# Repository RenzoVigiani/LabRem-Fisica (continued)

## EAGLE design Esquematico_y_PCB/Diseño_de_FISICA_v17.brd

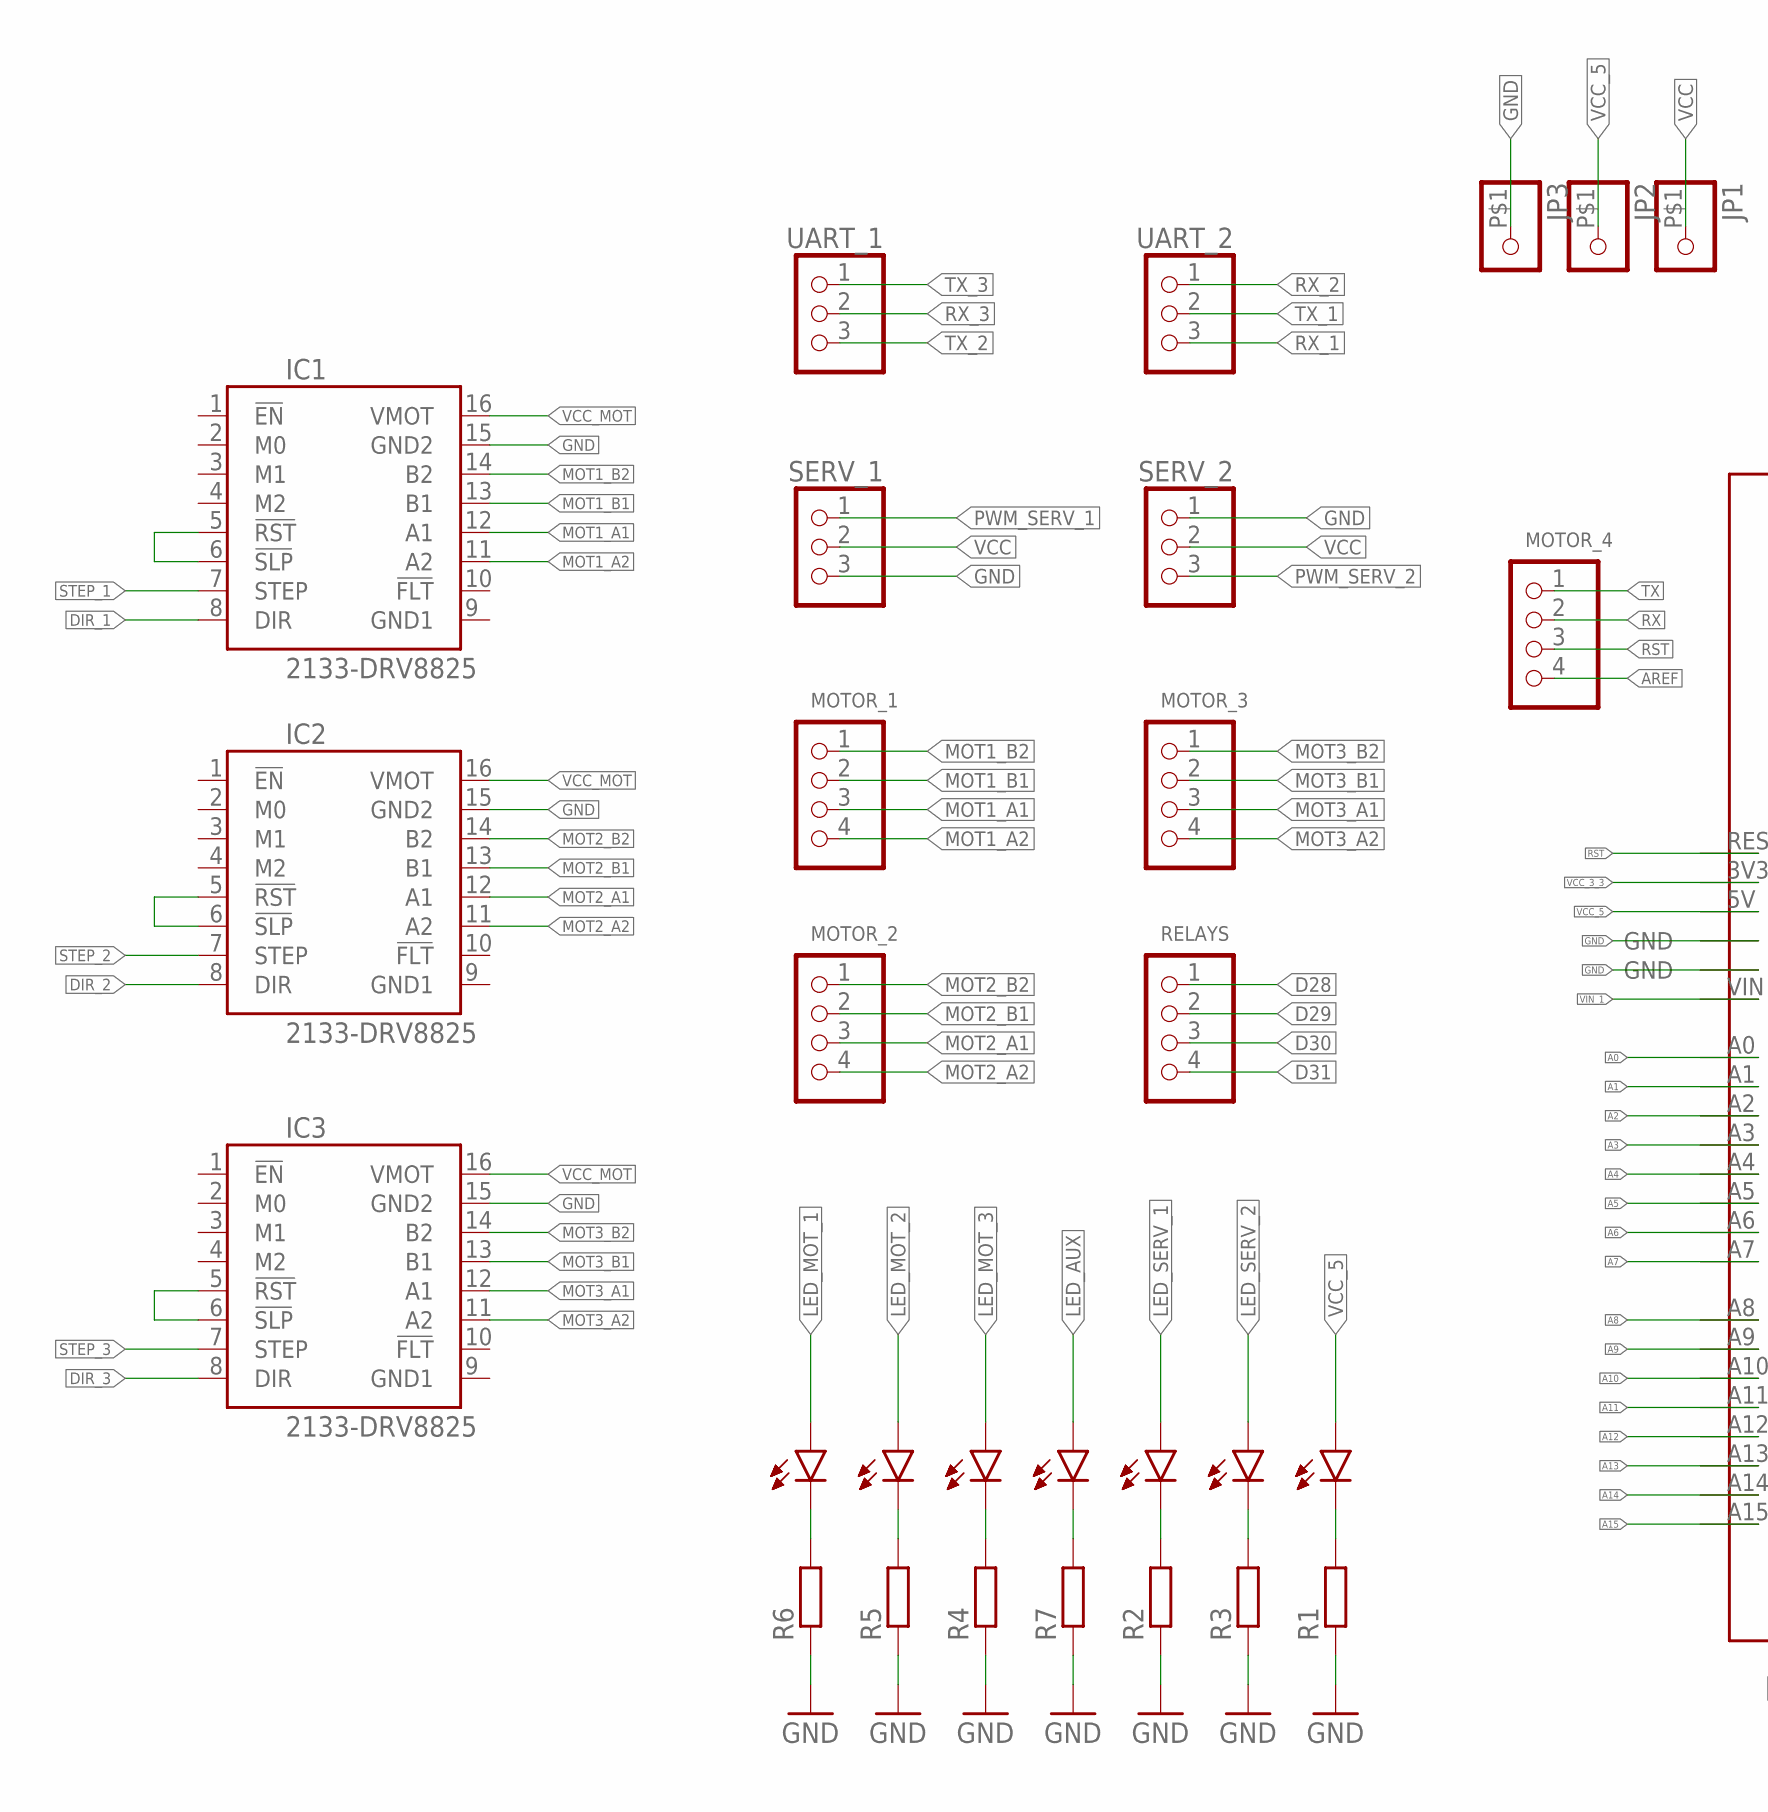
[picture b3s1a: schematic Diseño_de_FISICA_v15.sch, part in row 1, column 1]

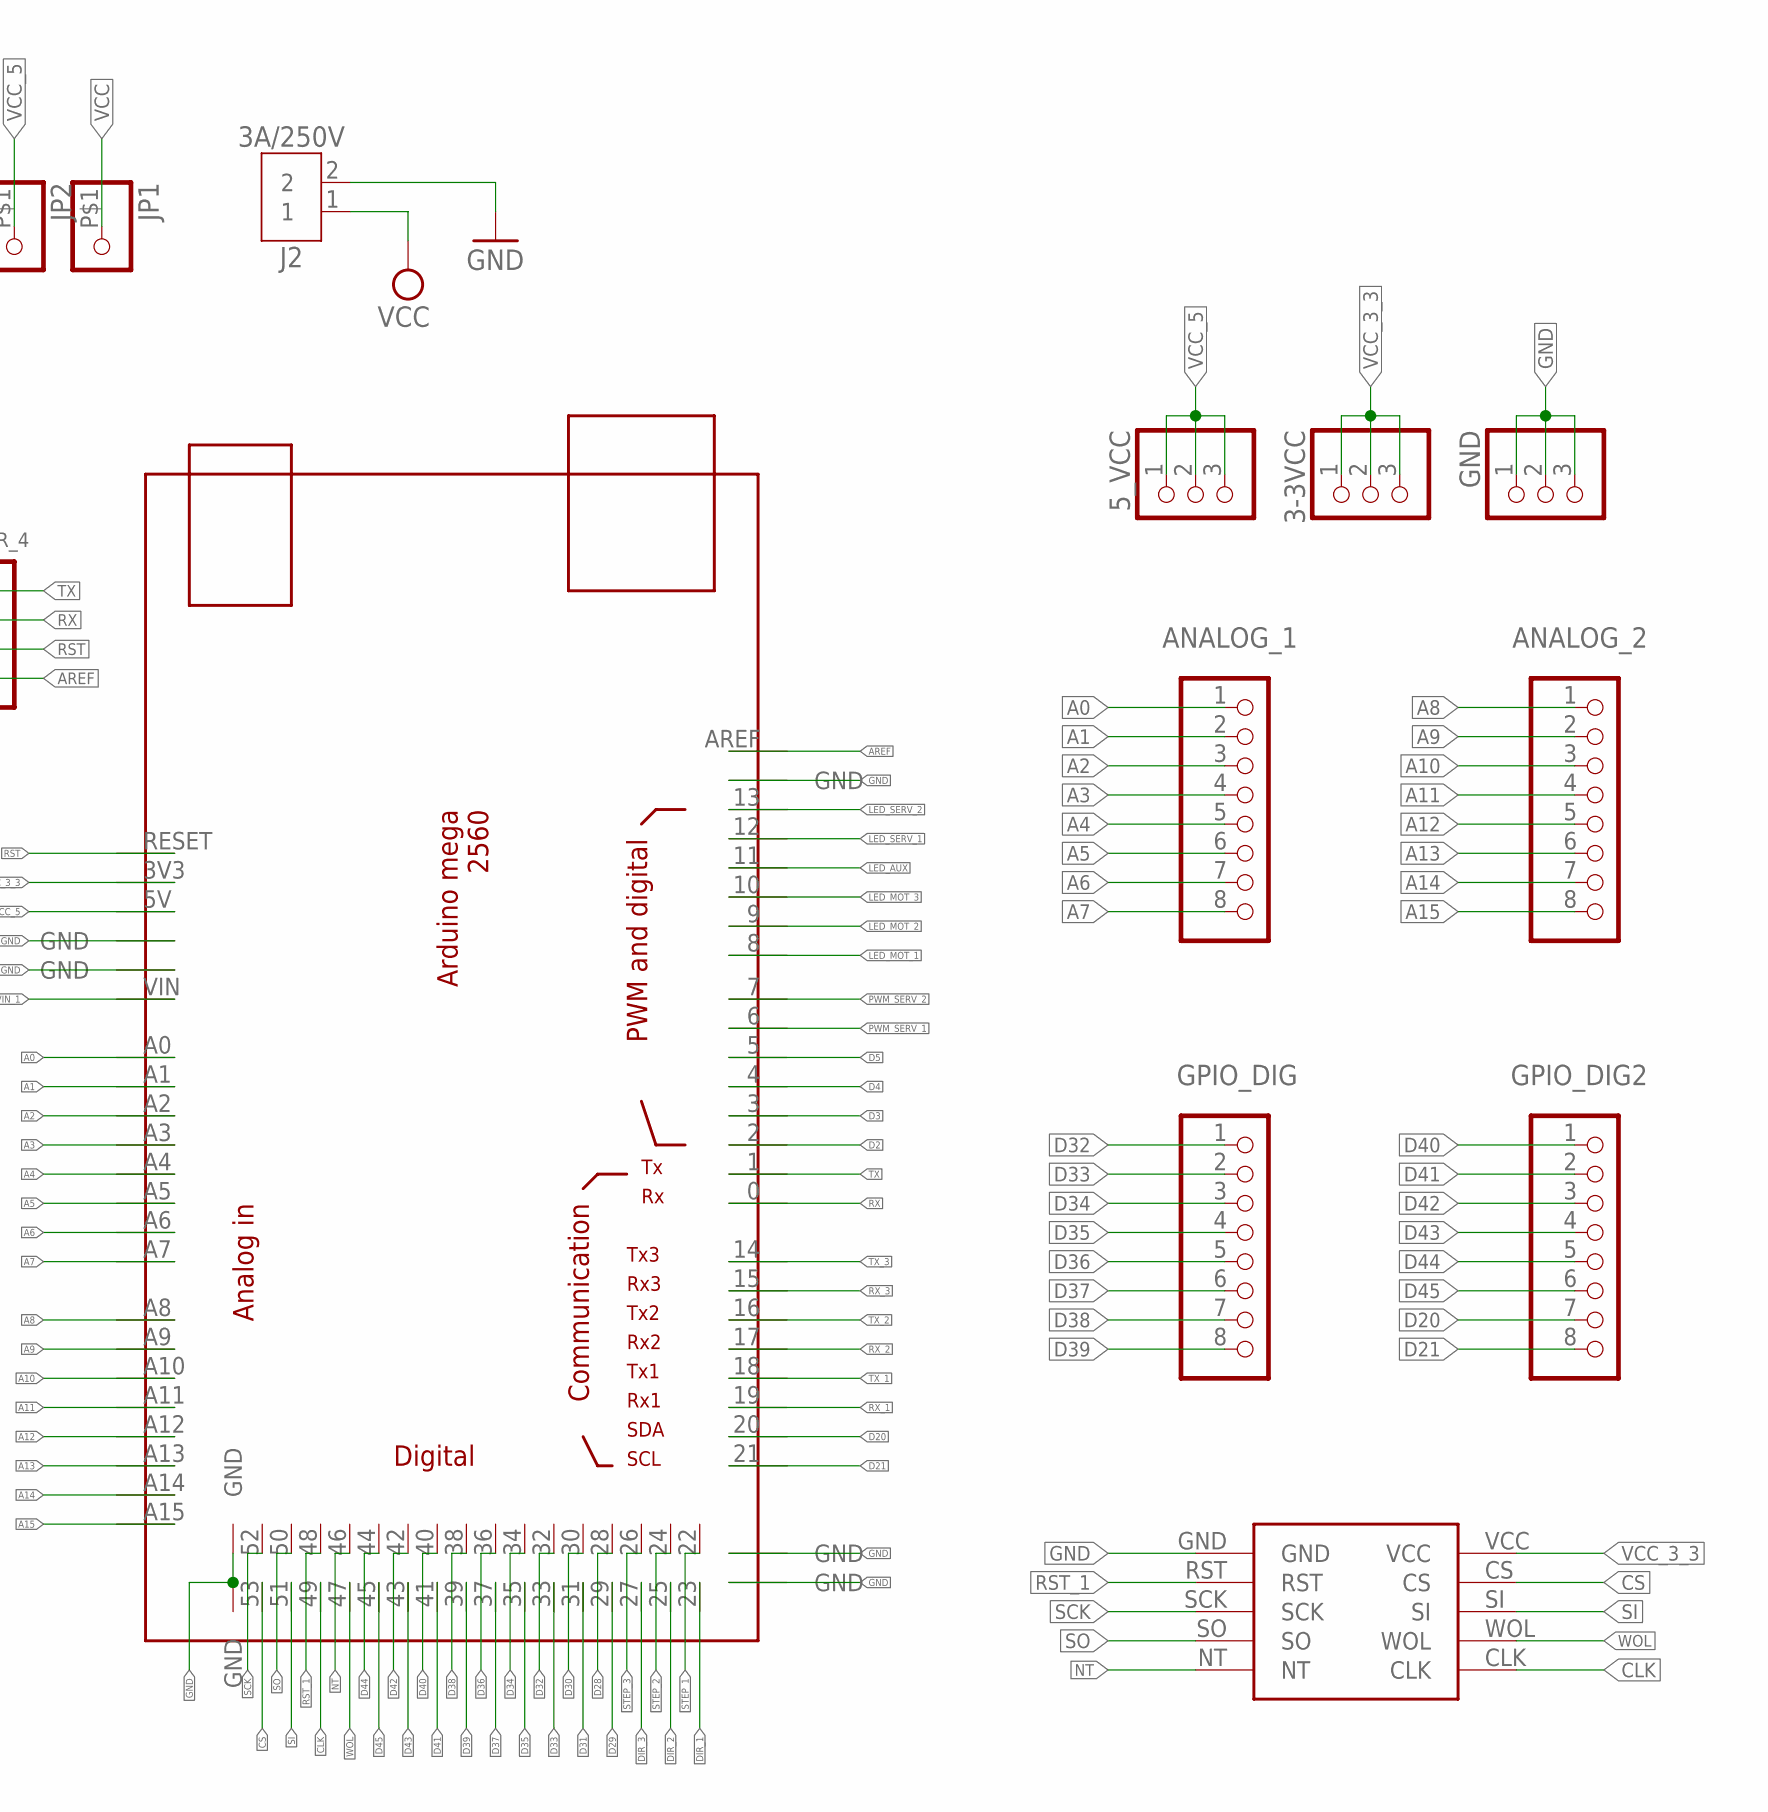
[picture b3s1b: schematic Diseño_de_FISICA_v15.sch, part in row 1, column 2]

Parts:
3-3VCC, 5_VCC: PINHD-1X3; 1X03
ANALOG_1, ANALOG_2: PINHD-1X8; 1X08
ARDUINOMEGA2560: MEGA_DEVICE; MEGAOUTLINE
GND: PINHD-1X3; 1X03
GPIO_DIG, GPIO_DIG2: PINHD-1X8; 1X08
IC1, IC2, IC3: 2133-DRV8825; DRV8825
J2: 3A/250V; B2B-XH-A
JP1, JP2, JP3: PINHD-1X1-BIGPOGO; 1X1-BIGPOGO
LED_AUX: LED_RED; LEDRD254W60D565H860B
LED_MOT1, LED_MOT2, LED_MOT3: LED_RED; LEDRD254W60D565H860B
LED_ON: LED_RED; LEDRD254W60D565H860B
LED_SERV1, LED_SERV2: LED_RED; LEDRD254W60D565H860B
MODULO_ETHERNET: ENC28J60
MOTOR_1, MOTOR_2, MOTOR_3, MOTOR_4: PINHD-1X4; 1X04
R1, R2, R3, R4, R5, R6, R7: R_CHIP-0805(2012-METRIC); RESC2012X65
RELAYS: PINHD-1X4; 1X04
SERV_1, SERV_2: PINHD-1X3; 1X03
UART_1, UART_2: PINHD-1X3; 1X03

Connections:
A0: ANALOG_1.1, ARDUINOMEGA2560.A0
A1: ANALOG_1.2, ARDUINOMEGA2560.A1
A2: ANALOG_1.3, ARDUINOMEGA2560.A2
A3: ANALOG_1.4, ARDUINOMEGA2560.A3
A4: ANALOG_1.5, ARDUINOMEGA2560.A4
A5: ANALOG_1.6, ARDUINOMEGA2560.A5
A6: ANALOG_1.7, ARDUINOMEGA2560.A6
A7: ANALOG_1.8, ARDUINOMEGA2560.A7
A8: ANALOG_2.1, ARDUINOMEGA2560.A8
A9: ANALOG_2.2, ARDUINOMEGA2560.A9
A10: ANALOG_2.3, ARDUINOMEGA2560.A10
A11: ANALOG_2.4, ARDUINOMEGA2560.A11
A12: ANALOG_2.5, ARDUINOMEGA2560.A12
A13: ANALOG_2.6, ARDUINOMEGA2560.A13
A14: ANALOG_2.7, ARDUINOMEGA2560.A14
A15: ANALOG_2.8, ARDUINOMEGA2560.A15
AREF: ARDUINOMEGA2560.AREF, MOTOR_4.4
CLK: ARDUINOMEGA2560.49, MODULO_ETHERNET.CLK
CS: ARDUINOMEGA2560.53, MODULO_ETHERNET.CS
D2: ARDUINOMEGA2560.2
D3: ARDUINOMEGA2560.3
D4: ARDUINOMEGA2560.4
D5: ARDUINOMEGA2560.5
D20: ARDUINOMEGA2560.20, GPIO_DIG2.7
D21: ARDUINOMEGA2560.21, GPIO_DIG2.8
D28: ARDUINOMEGA2560.28, RELAYS.1
D29: ARDUINOMEGA2560.29, RELAYS.2
D30: ARDUINOMEGA2560.30, RELAYS.3
D31: ARDUINOMEGA2560.31, RELAYS.4
D32: ARDUINOMEGA2560.32, GPIO_DIG.1
D33: ARDUINOMEGA2560.33, GPIO_DIG.2
D34: ARDUINOMEGA2560.34, GPIO_DIG.3
D35: ARDUINOMEGA2560.35, GPIO_DIG.4
D36: ARDUINOMEGA2560.36, GPIO_DIG.5
D37: ARDUINOMEGA2560.37, GPIO_DIG.6
D38: ARDUINOMEGA2560.38, GPIO_DIG.7
D39: ARDUINOMEGA2560.39, GPIO_DIG.8
D40: ARDUINOMEGA2560.40, GPIO_DIG2.1
D41: ARDUINOMEGA2560.41, GPIO_DIG2.2
D42: ARDUINOMEGA2560.42, GPIO_DIG2.3
D43: ARDUINOMEGA2560.43, GPIO_DIG2.4
D44: ARDUINOMEGA2560.44, GPIO_DIG2.5
D45: ARDUINOMEGA2560.45, GPIO_DIG2.6
DIR_1: ARDUINOMEGA2560.23, IC1.8 (DIR)
DIR_2: ARDUINOMEGA2560.25, IC2.8 (DIR)
DIR_3: ARDUINOMEGA2560.27, IC3.8 (DIR)
GND: ARDUINOMEGA2560.GND@1 (GND), ARDUINOMEGA2560.GND@2 (GND), ARDUINOMEGA2560.GND@3 (GND), ARDUINOMEGA2560.GND@4 (GND), ARDUINOMEGA2560.GND@5 (GND), ARDUINOMEGA2560.GND@6 (GND), ARDUINOMEGA2560.GND@7 (GND), GND.1, GND.2, GND.3, IC1.15 (GND2), IC2.15 (GND2), IC3.15 (GND2), J2.2, JP3.P$1, MODULO_ETHERNET.GND, R1.1, R2.1, R3.1, R4.1, R5.1, R6.1, R7.1, SERV_1.3, SERV_2.1
GND1: IC1.9 (GND1), IC2.9 (GND1), IC3.9 (GND1)
LED_AUX: ARDUINOMEGA2560.11, LED_AUX.1 (A)
LED_MOT_1: ARDUINOMEGA2560.8, LED_MOT1.1 (A)
LED_MOT_2: ARDUINOMEGA2560.9, LED_MOT2.1 (A)
LED_MOT_3: ARDUINOMEGA2560.10, LED_MOT3.1 (A)
LED_SERV_1: ARDUINOMEGA2560.12, LED_SERV1.1 (A)
LED_SERV_2: ARDUINOMEGA2560.13, LED_SERV2.1 (A)
MOT1_A1: IC1.12 (A1), MOTOR_1.3
MOT1_A2: IC1.11 (A2), MOTOR_1.4
MOT1_B1: IC1.13 (B1), MOTOR_1.2
MOT1_B2: IC1.14 (B2), MOTOR_1.1
MOT2_A1: IC2.12 (A1), MOTOR_2.3
MOT2_A2: IC2.11 (A2), MOTOR_2.4
MOT2_B1: IC2.13 (B1), MOTOR_2.2
MOT2_B2: IC2.14 (B2), MOTOR_2.1
MOT3_A1: IC3.12 (A1), MOTOR_3.3
MOT3_A2: IC3.11 (A2), MOTOR_3.4
MOT3_B1: IC3.13 (B1), MOTOR_3.2
MOT3_B2: IC3.14 (B2), MOTOR_3.1
unnamed: IC2.5 (!RST), IC2.6 (!SLP)
unnamed: IC1.5 (!RST), IC1.6 (!SLP)
unnamed: IC3.5 (!RST), IC3.6 (!SLP)
unnamed: LED_ON.2 (C), R1.2
unnamed: LED_SERV1.2 (C), R2.2
unnamed: LED_SERV2.2 (C), R3.2
unnamed: LED_MOT3.2 (C), R4.2
unnamed: LED_MOT2.2 (C), R5.2
unnamed: LED_MOT1.2 (C), R6.2
unnamed: LED_AUX.2 (C), R7.2
NT: ARDUINOMEGA2560.46, MODULO_ETHERNET.NT
PWM_SERV_1: ARDUINOMEGA2560.6, SERV_1.1
PWM_SERV_2: ARDUINOMEGA2560.7, SERV_2.3
RST: ARDUINOMEGA2560.RESET, MOTOR_4.3
RST_1: ARDUINOMEGA2560.48, MODULO_ETHERNET.RST
RX: ARDUINOMEGA2560.0, MOTOR_4.2
RX_1: ARDUINOMEGA2560.19, UART_2.3
RX_2: ARDUINOMEGA2560.17, UART_2.1
RX_3: ARDUINOMEGA2560.15, UART_1.2
SCK: ARDUINOMEGA2560.52, MODULO_ETHERNET.SCK
SI: ARDUINOMEGA2560.51, MODULO_ETHERNET.SI
SO: ARDUINOMEGA2560.50, MODULO_ETHERNET.SO
STEP_1: ARDUINOMEGA2560.22, IC1.7 (STEP)
STEP_2: ARDUINOMEGA2560.24, IC2.7 (STEP)
STEP_3: ARDUINOMEGA2560.26, IC3.7 (STEP)
TX: ARDUINOMEGA2560.1, MOTOR_4.1
TX_1: ARDUINOMEGA2560.18, UART_2.2
TX_2: ARDUINOMEGA2560.16, UART_1.3
TX_3: ARDUINOMEGA2560.14, UART_1.1
VCC: J2.1, JP1.P$1, SERV_1.2, SERV_2.2
VCC_3_3: 3-3VCC.1, 3-3VCC.2, 3-3VCC.3, ARDUINOMEGA2560.3V3, MODULO_ETHERNET.VCC
VCC_5: 5_VCC.1, 5_VCC.2, 5_VCC.3, ARDUINOMEGA2560.5V, JP2.P$1, LED_ON.1 (A)
VCC_MOT: IC1.16 (VMOT), IC2.16 (VMOT), IC3.16 (VMOT)
VIN_1: ARDUINOMEGA2560.VIN
WOL: ARDUINOMEGA2560.47, MODULO_ETHERNET.WOL

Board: 2 copper layers, 39 parts (0 on the bottom side), 96 nets, no tracks yet.

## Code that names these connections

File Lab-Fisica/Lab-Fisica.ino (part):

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  #define M3_Step 36
  #define M3_Direction 37
//---Enables
  #define M1_Enable 28
  #define M2_Enable 32
  #define M3_Enable 35
//----------------------------------------------//
//SERVOS
//---Leds 
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  Servo servo_lente;
//----------------------------------------------//
//FOCO - LAMPARA LED 3W
  #define Foco_pin 48 // Pin para habilitar relay de lampara.
//----------------------------------------------//
//Sentidos
  #define AntiHorario HIGH
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// Motor 1
  pinMode(M1_Step, OUTPUT);
  pinMode(M1_Direction, OUTPUT);
  pinMode(M1_Enable, OUTPUT); // Enable Motor 1
  pinMode(M1_SW_inicio,INPUT_PULLUP);
  pinMode(M1_SW_fin,INPUT_PULLUP);
// Motor 2
  pinMode(M2_Step, OUTPUT);
  pinMode(M2_Direction, OUTPUT);
  pinMode(M2_Enable, OUTPUT); // Enable Motor 2
  pinMode(M2_SW_inicio,INPUT_PULLUP);
  pinMode(M2_SW_fin,INPUT_PULLUP);
// Motor 3
  pinMode(M3_Step, OUTPUT);
  pinMode(M3_Direction, OUTPUT);
  pinMode(M3_Enable, OUTPUT); // Enable Motor 3
  pinMode(M3_SW_inicio,INPUT_PULLUP);
  pinMode(M3_SW_fin,INPUT_PULLUP);
  // Leds
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  pinMode(S_Diafragma_Led, OUTPUT); // Led Servo 1
  pinMode(S_Lente_Led, OUTPUT); // Led Servo 2
 // Foco (LED)
  pinMode(Foco_pin, OUTPUT);
// Servos
  servo_diafragma.attach(S_Diafragma_Pin);
  servo_lente.attach(S_Lente_Pin);
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 * @param distancia_l2p indica la distancia entre lente y pantalla
 */
void Convergentes(int diafragma, int distancia_fl2, int distancia_l2p){
  digitalWrite(Foco_pin, HIGH); // Enciendo FOCO
  mover_servo(servo_lente,90); // Lente desactivado
  switch (diafragma){ // Posicion del diafragma
    case 0: mover_servo(servo_diafragma,0);// Desplazamos a la posición 0º
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
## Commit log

2022-04-28 Init Commit
2022-04-28 control
2022-04-28 vscode
2022-04-28 Agregado de imagenes al readme.md
2022-04-28 readme.md
2022-04-28 unificacion de criterios
2022-04-28 nombre
2022-04-28 init commit C
2022-04-28 init commit d
2022-04-28 ramas fusionadas
2022-05-05 Orden y adaptación de salidas y funciones
2022-05-05 Optimización de funciones y control de envio y recepcion de Json
2022-05-05 Movimiento de Motor resuelto Ver reporte de vueltas para analizar estado actual.
2022-05-05 Control de servo realizado Ya realiza el conteo de vueltas
2022-05-05 Surge un problema en Arduino UNO Cuando se usa casi el 90% de la memoria se traba en algunos procesos.
    controlar el GET
2022-05-06 Programación del arduino desde VSCode
2022-05-06 actualización Readme
2022-05-06 ajustes de funciones get y post Controlar las distancias de cada motor.
2022-05-08 Ajustes en readme
2022-05-09 Definición de distancias máx y mín
2022-05-09 Control de distancias solucionado
2022-05-09 init change in divergentes
2022-05-10 Ajustes Divergente
2022-05-11 Ajustes de pines para Arduino Mega
2022-05-27 Datasheet-ServoMG996R
2022-05-27 carga de esquematico tentativo
2022-05-27 Incorporación Archivos esquematicos
2022-05-31 Carga de diseños pcb
2022-05-31 PCB casi terminado - Controlar y corregir
2022-06-02 PDF of schematic and board
2022-06-02 Protocolo de comunicación Programa usado para controlar las formas de comunicación
2022-06-03 Control de protocolo con nueva librería
2022-06-06 Diseño de control generico terminado.
2022-06-06 Lab-Fisica protocolo actualizado. Control de movimiento
2022-06-16 Protocolo - Pruebas con Ethercard y el diseño del programa
2022-07-01 Prueba de webSocket
2022-07-01 websocket
2022-07-01 Pruebas de WebSocket Quizas no sirve para lo que necesitamos
2022-07-03 Protocolo de comunicación Se realizó la actualización del protocolo de comunicación
2022-07-04 Programa funcionando Queda corregir algunos detalles del control de distancias y las banderas
2022-07-05 Actualización de Protocolo Está funcionando el programa para arduino. y el protocolo de comunicación. No se desconecta.
2022-07-06 cambios en esquematico y pcb
2022-07-12 esquematico y board exportados
2022-07-13 esquematico actualizado
2022-07-13 export sch
2022-07-14 Actualización de descripciones Se actualizaron las descripciones de las funciones y detalles
2022-07-14 Actualización readme y esquematico
2022-07-14 img del esquematico
2022-07-21 Primera PCB
2022-07-21 Acualización PCB y SCH
2022-08-17 Modificación 2
2022-09-13 cambios PCB
2022-09-14 Actualización de manejo de motores Pruebas con servos
2022-09-15 modificación esquematico
2022-09-15 modificaciones Fisica.ino
2022-09-15 Modif PCB
2022-09-16 PCB Corregidas
2022-09-16 Diseño PCB full
2022-09-16 Correcciones PCB
2022-09-16 diseños 3d
2022-09-18 Modificaciones para control de distancias y readme
2022-09-19 diseño 3D SisCom
2022-09-20 Ultimos detalles motorees
2022-09-20 Ajuste pos inicial de servos en 90. Actualizacion de imagenes de placa
2022-09-21 NuevosDiseños 3D
2022-09-22 impresiones 3d - ver motores cuando cambian juntos
2022-09-22 Diseños_3D
2022-09-29 Diseños3D
2022-11-23 Agregados de imagenes y actualización Readme.md
2022-11-24 Fotos agregadas
2022-11-24 cambios en readme.md actualización de imagenes
2022-11-24 Readme.md actualizado
